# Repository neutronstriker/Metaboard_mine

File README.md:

Metaboard_mine
==============

A custom designed dev. board for 28-pin AVR micro-controllers.

I designed this board after finding the Metaboard design. 

Find more info about this at http://www.xmechatronics.com/2014/12/avr-28-pin-development-board-with-usb.html

<br /><span xmlns:dct="http://purl.org/dc/terms/" property="dct:title">metaboard_mine</span> by <span xmlns:cc="http://creativecommons.org/ns#" property="cc:attributionName">NeutroN StrikeR</span> is licensed under a <a rel="license" href="http://creativecommons.org/licenses/by-sa/4.0/">Creative Commons Attribution-ShareAlike 4.0 International License</a>.

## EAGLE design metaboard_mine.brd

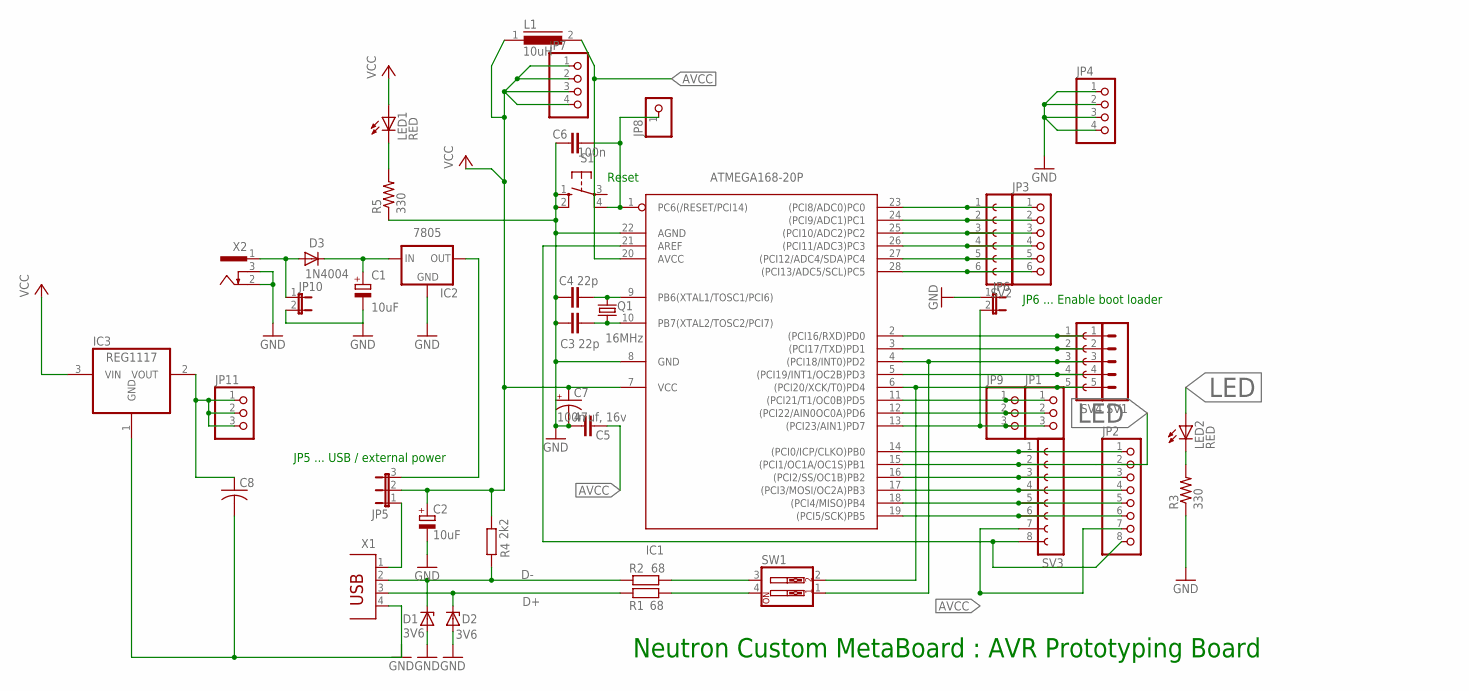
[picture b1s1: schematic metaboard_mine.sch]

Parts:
C1: 10uF; E3,5-10
C2: 10uF; E2,5-6E
C3, C4: 22p; C025-024X044
C5, C6: 100n; C050-025X075
C7: 47uf, 16v; E2,5-6
C8: C-USC0805K; C0805K
D1, D2: 3V6; DO34Z7
D3: 1N4004; DO41-10
IC1: ATMEGA168-20P; DIL28-3
IC2: 7805; 78XXL
IC3: REG1117; SOT223
JP1, JP9, JP11: PINHD-1X3; 1X03
JP2: PINHD-1X8; 1X08
JP3: PINHD-1X6; 1X06
JP4, JP7: PINHD-1X4; 1X04
JP5: JP2E; JP2
JP6, JP10: JP1E; JP1
JP8: PINHD-1X1; 1X01
L1: 10uH; MICC12
LED1: RED; LED5MM
LED2: RED; LED3MM
Q1: 16MHz; HC49/S
R1, R2: 68; 0207/10
R3, R5: 330; 0207/10
R4: 2k2; 0207/10
S1: 10-XX; B3F-10XX
SV1: MA05-1
SV2: FE06-1; FE06
SV3: FE08-1; FE08
SV4: FE05-1
SW1: SW_DIP-2; EDG-02
X1: PN61729
X2: 733980-62

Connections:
+5USB: JP5.1, X1.1
+VRAW: C1.+, D3.C, IC2.IN
AVCC: C5.1, IC1.20 (AVCC), JP2.7, L1.2, SV3.7
D+: D2.C, R1.1, X1.3
D-: D1.C, R2.1, R4.2, X1.2
GND: IC2.GND
LED: IC1.15 ((PCI1/OC1A/OC1S)PB1), JP2.2, LED2.A, SV3.2
unnamed: IC1.6 ((PCI20/XCK/T0)PD4), SV1.5, SV4.5, SW1.2
unnamed: C6.2, IC1.1 (PC6(/RESET/PCI14)), JP8.1, S1.4 (P1)
unnamed: IC1.4 ((PCI18/INT0)PD2), SV1.3, SV4.3, SW1.1
unnamed: D3.A, JP10.1, X2.1
unnamed: R2.2, SW1.3
unnamed: IC1.2 ((PCI16/RXD)PD0), SV1.1, SV4.1
unnamed: R1.2, SW1.4
unnamed: IC2.OUT, JP5.3
unnamed: C3.2, IC1.10 (PB7(XTAL2/TOSC2/PCI7)), Q1.1
unnamed: C4.2, IC1.9 (PB6(XTAL1/TOSC1/PCI6)), Q1.2
unnamed: IC1.3 ((PCI17/TXD)PD1), SV1.2, SV4.2
unnamed: IC1.5 ((PCI19/INT1/OC2B)PD3), SV1.4, SV4.4
unnamed: IC1.11 ((PCI21/T1/OC0B)PD5), JP1.1, JP9.1
unnamed: IC1.12 ((PCI22/AIN0OC0A)PD6), JP1.2, JP9.2
unnamed: IC1.13 ((PCI23/AIN1)PD7), JP1.3, JP6.2, JP9.3
unnamed: IC1.23 ((PCI8/ADC0)PC0), JP3.1, SV2.1
unnamed: IC1.24 ((PCI9/ADC1)PC1), JP3.2, SV2.2
unnamed: IC1.25 ((PCI10/ADC2)PC2), JP3.3, SV2.3
unnamed: IC1.26 ((PCI11/ADC3)PC3), JP3.4, SV2.4
unnamed: IC1.27 ((PCI12/ADC4/SDA)PC4), JP3.5, SV2.5
unnamed: IC1.28 ((PCI13/ADC5/SCL)PC5), JP3.6, SV2.6
unnamed: LED2.K (C), R3.2
unnamed: IC1.16 ((PCI2/SS/OC1B)PB2), JP2.3, SV3.3
unnamed: IC1.17 ((PCI3/MOSI/OC2A)PB3), JP2.4, SV3.4
unnamed: IC1.18 ((PCI4/MISO)PB4), JP2.5, SV3.5
unnamed: IC1.19 ((PCI5/SCK)PB5), JP2.6, SV3.6
unnamed: LED1.K (C), R5.2
unnamed: IC1.21 (AREF), JP2.8, SV3.8
unnamed: IC1.14 ((PCI0/ICP/CLKO)PB0), JP2.1, SV3.1
unnamed: C1.-, C2.-, C3.1, C4.1, C5.2, C6.1, C7.-, C8.2, D1.A, D2.A, IC1.8 (GND), IC1.22 (AGND), IC3.1 (GND), JP4.1, JP4.2, JP4.3, JP4.4, JP6.1, JP10.2, R3.1, R5.1, S1.1 (S), S1.2 (S1), X1.4, X2.2, X2.3
unnamed: C8.1, IC3.2 (VOUT), JP11.1, JP11.2, JP11.3
VCC: C2.+, C7.+, IC1.7 (VCC), IC3.3 (VIN), JP5.2, JP7.1, JP7.2, JP7.3, JP7.4, L1.1, LED1.A, R4.1

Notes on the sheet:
JP5 ... USB / external power
JP6 ... Enable boot loader
Reset
Neutron Custom MetaBoard : AVR Prototyping Board

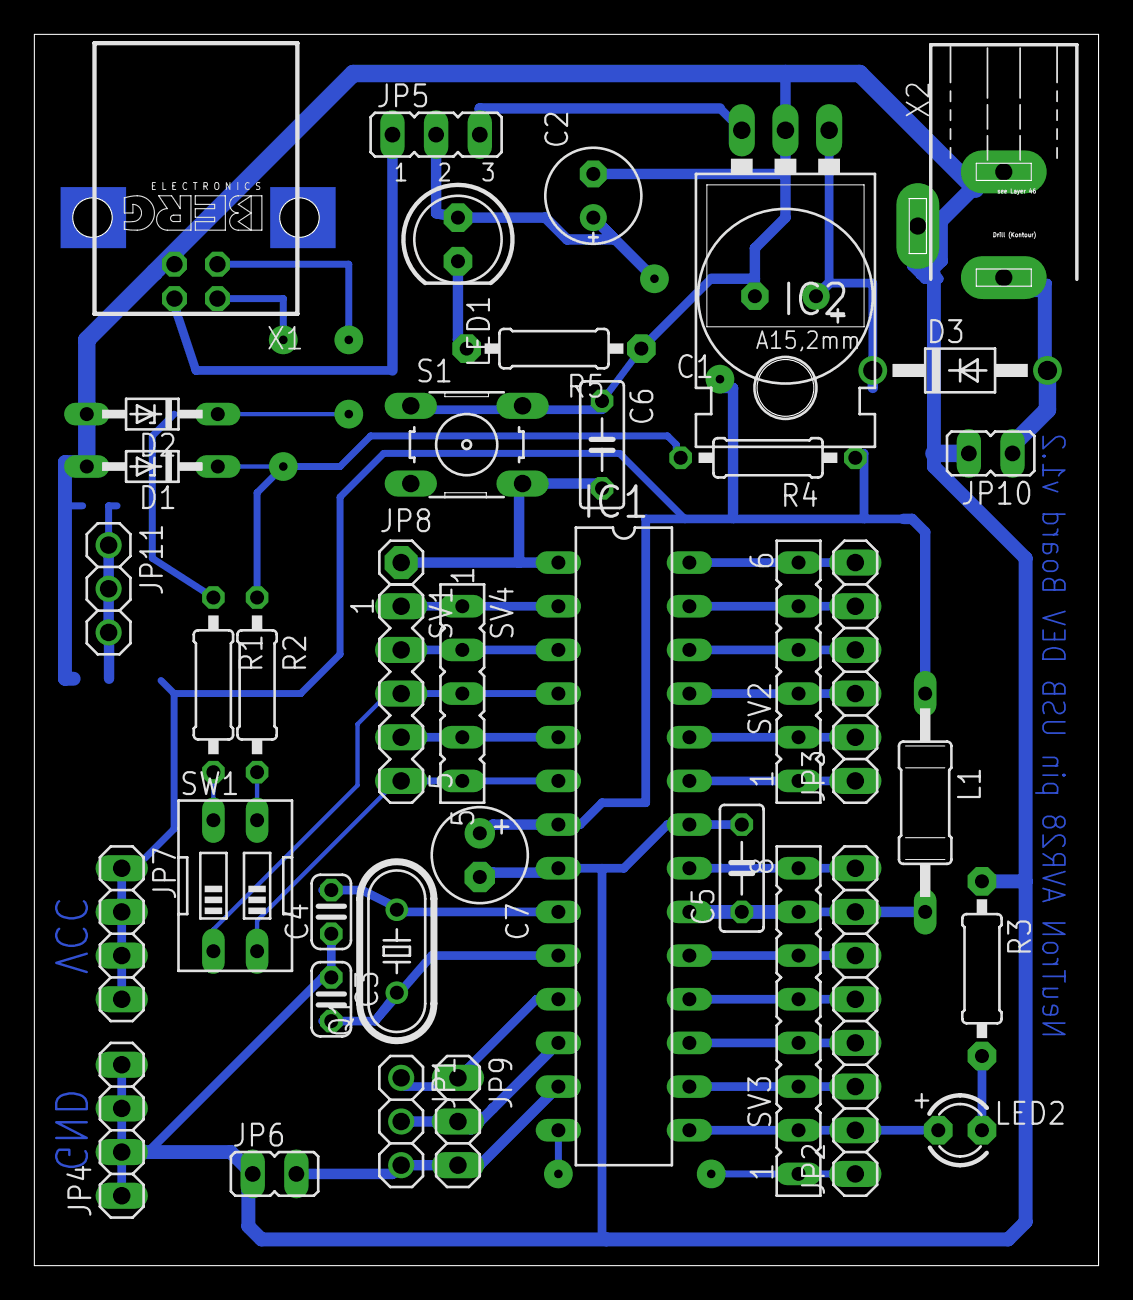
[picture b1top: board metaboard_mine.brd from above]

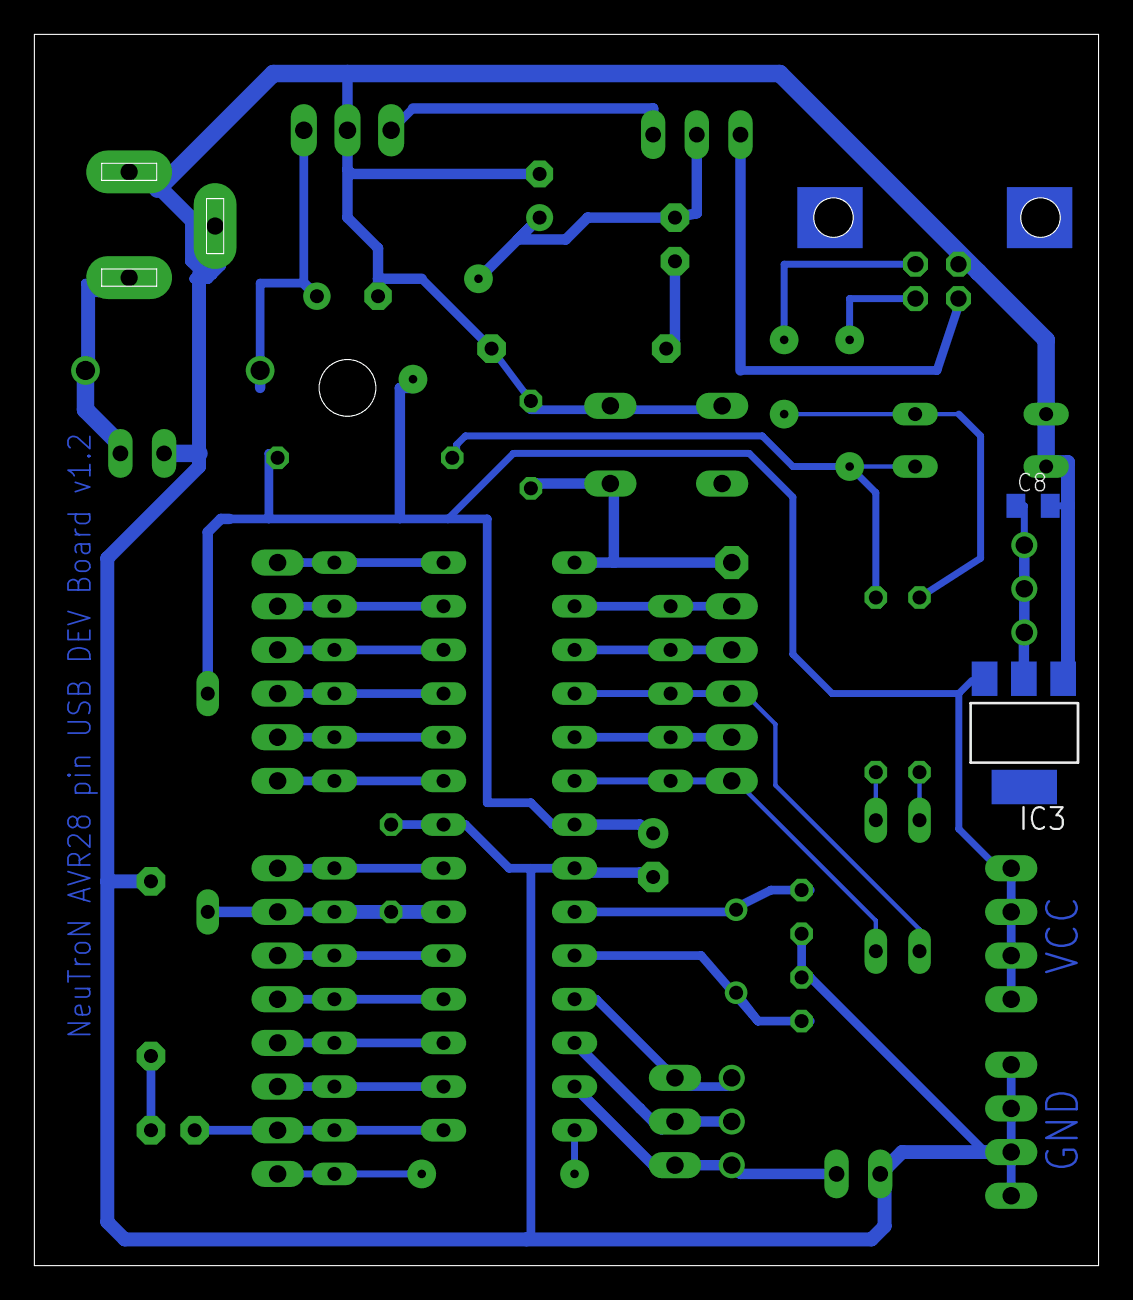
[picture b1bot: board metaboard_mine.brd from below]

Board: 2 copper layers, 61.9 x 71.6 mm, 42 parts (2 on the bottom side), 38 nets.

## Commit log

2014-12-28 :circus_tent: Added .gitattributes & .gitignore files
2014-12-28 added design files
2014-12-28 deleted backups
2014-12-28 added sch prnt
